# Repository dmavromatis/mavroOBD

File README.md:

# mavroOBD
Arduino (328P) based OBD port module

The goal of this project it to create an Arduino based OBD port module that can be used to enhance a vehicles capabilites.  For example, if you want door locks to close when moving faster than 5mph or to invoke/emulate certain CANbus buttons automatically at start up.

I have uploaded board designs for an OBD module I puchased from China.  It's a two board design.  Lower board solders to the pins of the OBD module and provides a 12V > 5V power supply.  Headers connect to the top board where the Atmel 328P and Microchip MCP2515 CAN Bus controller with SPI interface and MCP2551 CAN transceiver.

This project is based on an Arduino Uno and SeedStudio CAN shield just miniturized to fit in a OBD module.

The module enclousure was purchased from a company in China called AOTAI Industry Co.<br>
Part #: AOT-130N - ODB Connector with housing<br/>
Website: www.aotsisz.com

--------
License
--------

If you are distributing a modified version of the project, please describe the dates and details of your modifications (as described in section 3.3b of the CERN open hardware license).  If you are using a publicly available repository to track changes (which we encourage), you may simply list the URL of the repository here.

https://github.com/dmavromatis/mavroOBD

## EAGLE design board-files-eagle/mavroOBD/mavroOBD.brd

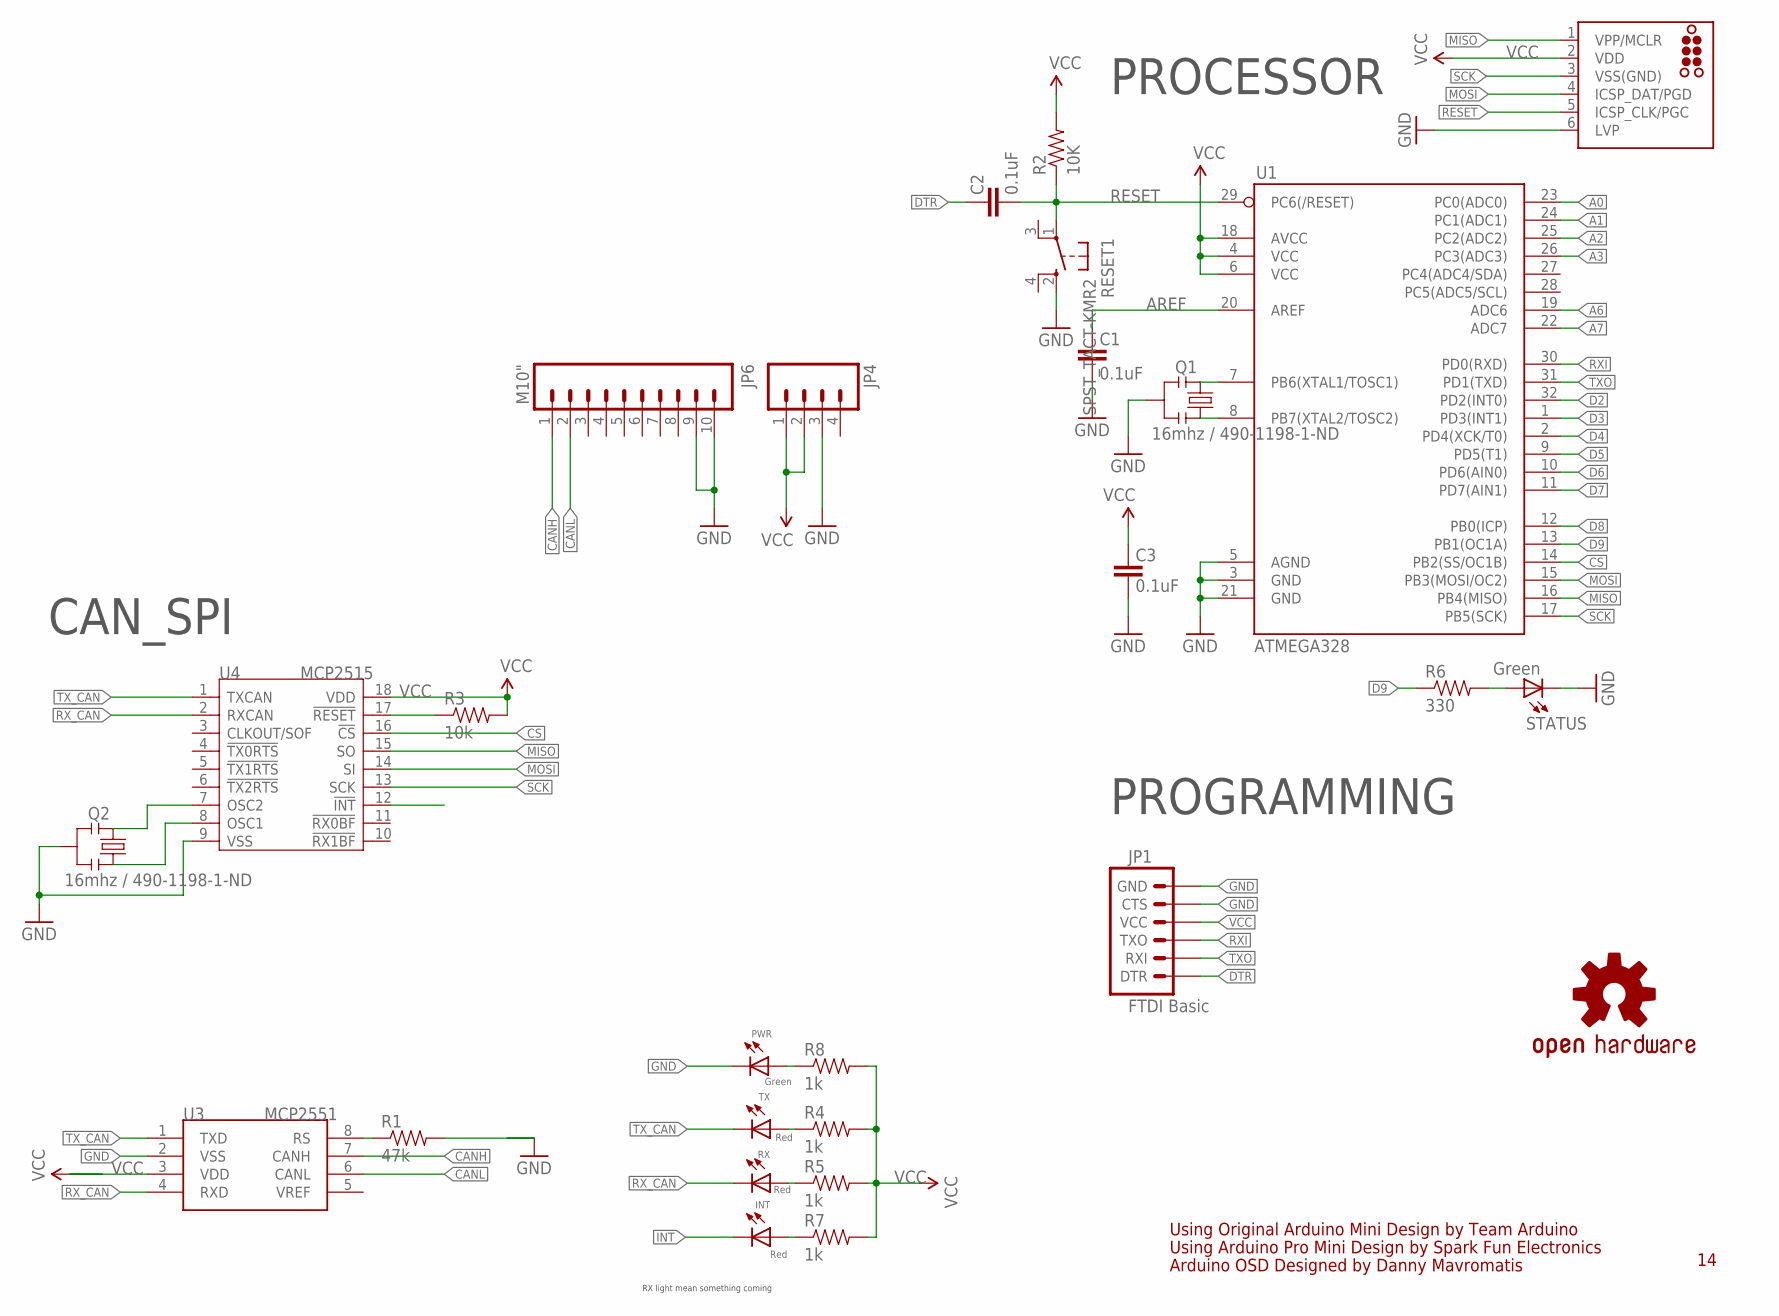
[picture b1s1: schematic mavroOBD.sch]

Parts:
C1, C2, C3: 0.1uF; 0603-CAP
INT: Red; 0603-LED-ALT1
J1: TC2030-MCP-NL
JP1: FTDI Basic; 1X06
JP4: M04PTH; 1X04
JP6: M10"; 1X10
PWR: Green; 0603-LED-ALT1
Q1, Q2: 16mhz / 490-1198-1-ND; RESONATOR-SMD-1:1
R1: 47k; 0603-RES
R2: 10K; 0603-RES
R3: 10k; 0603-RES
R4, R5, R7, R8: 1k; 0603-RES
R6: 330; 0603-RES
RESET1: SPST_TACT-KMR2; KMR2
RX: Red; 0603-LED-ALT1
STATUS: Green; 0603-LED-ALT1
TX: Red; 0603-LED-ALT1
U1: ATMEGA328; TQFP32-08
U3: MCP2551; SOIC8-6.0
U4: MCP2515; SOIC18
U$3: OSHW-LOGOS; OSHW-LOGO-S

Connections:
A0: U1.23 (PC0(ADC0))
A1: U1.24 (PC1(ADC1))
A2: U1.25 (PC2(ADC2))
A3: U1.26 (PC3(ADC3))
A6: U1.19 (ADC6)
A7: U1.22 (ADC7)
AREF: C1.2, U1.20 (AREF)
CANH: JP6.1, U3.7 (CANH)
CANL: JP6.2, U3.6 (CANL)
CS: U1.14 (PB2(SS/OC1B)), U4.16 (!CS)
D2: U1.32 (PD2(INT0))
D3: U1.1 (PD3(INT1))
D4: U1.2 (PD4(XCK/T0))
D5: U1.9 (PD5(T1))
D6: U1.10 (PD6(AIN0))
D7: U1.11 (PD7(AIN1))
D8: U1.12 (PB0(ICP))
D9: R6.1, U1.13 (PB1(OC1A))
DTR: C2.2, JP1.1 (DTR)
GND: C1.1, C3.1, J1.6 (LVP), JP1.5 (CTS), JP1.6 (GND), JP4.3, JP6.9, JP6.10, PWR.C, Q1.2, Q2.2, R1.2, RESET1.2 (S), STATUS.C, U1.3 (GND), U1.5 (AGND), U1.21 (GND), U3.2 (VSS), U4.9 (VSS)
INT: INT.C, U4.12 (!INT)
MISO: J1.1 (VPP/MCLR), U1.16 (PB4(MISO)), U4.15 (SO)
MOSI: J1.4 (ICSP_DAT/PGD), U1.15 (PB3(MOSI/OC2)), U4.14 (SI)
unnamed: Q1.3, U1.8 (PB7(XTAL2/TOSC2))
unnamed: Q1.1, U1.7 (PB6(XTAL1/TOSC1))
unnamed: R4.1, TX.A
unnamed: PWR.A, R8.1
unnamed: R6.2, STATUS.A
unnamed: R5.1, RX.A
unnamed: Q2.1, U4.7 (OSC2)
unnamed: Q2.3, U4.8 (OSC1)
unnamed: INT.A, R7.1
unnamed: R1.1, U3.8 (RS)
RESET: C2.1, J1.5 (ICSP_CLK/PGC), R2.1, RESET1.1, U1.29 (PC6(/RESET))
RST_N: R3.1, U4.17 (!RESET)
RXI: JP1.3 (TXO), U1.30 (PD0(RXD))
RX_CAN: RX.C, U3.4 (RXD), U4.2 (RXCAN)
SCK: J1.3 (VSS(GND)), U1.17 (PB5(SCK)), U4.13 (SCK)
TXO: JP1.2 (RXI), U1.31 (PD1(TXD))
TX_CAN: TX.C, U3.1 (TXD), U4.1 (TXCAN)
VCC: C3.2, J1.2 (VDD), JP1.4 (VCC), JP4.1, JP4.2, R2.2, R3.2, R4.2, R5.2, R7.2, R8.2, U1.4 (VCC), U1.6 (VCC), U1.18 (AVCC), U3.3 (VDD), U4.18 (VDD)

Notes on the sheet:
Using Original Arduino Mini Design by Team Arduino
Using Arduino Pro Mini Design by Spark Fun Electronics
CAN_SPI
RX light mean something coming
PROGRAMMING
PROCESSOR
Arduino OSD Designed by Danny Mavromatis

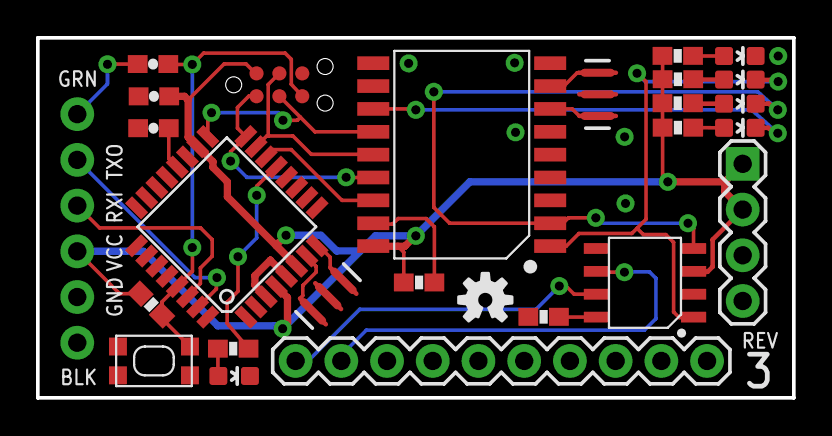
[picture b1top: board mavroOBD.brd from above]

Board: 2 copper layers, 42.0 x 20.0 mm, 27 parts (1 on the bottom side), 28 nets.

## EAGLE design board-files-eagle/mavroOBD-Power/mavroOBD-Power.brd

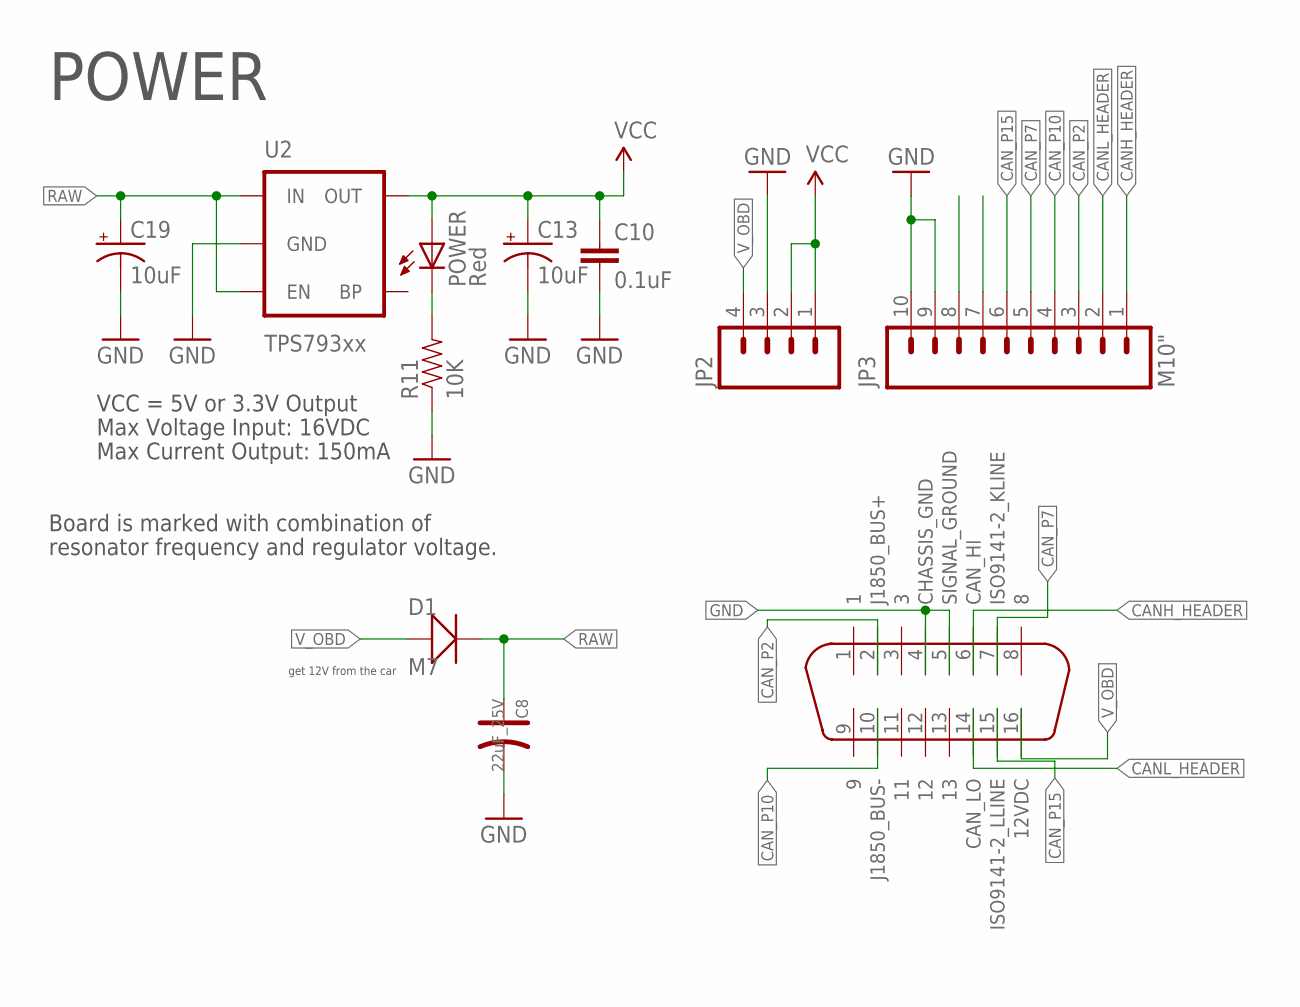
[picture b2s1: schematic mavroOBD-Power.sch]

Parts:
C8: 22uF_25V; ELECTRO-SMD-B-4.8MM
C10: 0.1uF; 0603-CAP
C13, C19: 10uF; EIA3216
D1: M7; D2010
JP2: M04PTH; 1X04
JP3: M10"; 1X10
POWER: Red; 0603-LED-ALT1
R11: 10K; 0603-RES
U2: TPS793xx; SOT23-5
U$1: ODBII-CON; OBDII-CON

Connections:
CANH_HEADER: JP3.1, U$1.6 (CAN_HI)
CANL_HEADER: JP3.2, U$1.14 (CAN_LO)
CAN_P2: JP3.3, U$1.2 (J1850_BUS+)
CAN_P7: JP3.5, U$1.7 (ISO9141-2_KLINE)
CAN_P10: JP3.4, U$1.10 (J1850_BUS-)
CAN_P15: JP3.6, U$1.15 (ISO9141-2_LLINE)
GND: C8.-, C10.2, C13.C (-), C19.C (-), JP2.3, JP3.9, JP3.10, R11.1, U2.2 (GND), U$1.4 (CHASSIS_GND), U$1.5 (SIGNAL_GROUND)
unnamed: POWER.C, R11.2
RAW: C8.+, C19.A (+), D1.-, U2.1 (IN), U2.3 (EN)
VCC_MAIN: C10.1, C13.A (+), JP2.1, JP2.2, POWER.A, U2.5 (OUT)
V_OBD: D1.+, JP2.4, U$1.16 (12VDC)

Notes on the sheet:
Max Voltage Input: 16VDC
Max Current Output: 150mA
Board is marked with combination of
resonator frequency and regulator voltage.
VCC = 5V or 3.3V Output
get 12V from the car
POWER

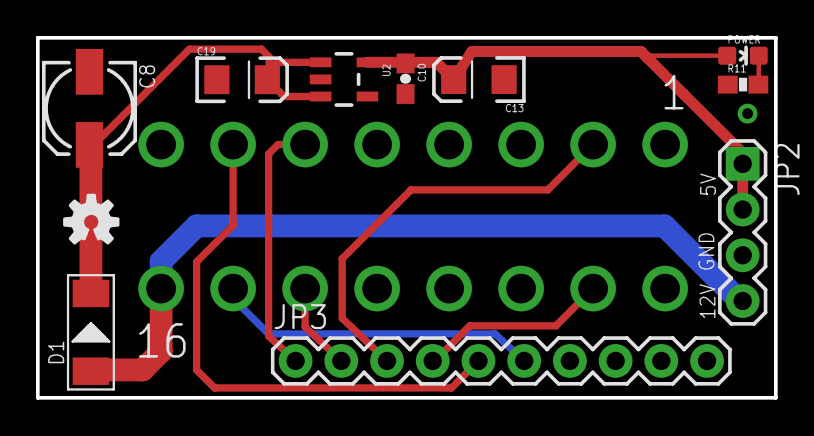
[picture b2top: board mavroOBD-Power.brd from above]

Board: 2 copper layers, 41.0 x 20.0 mm, 12 parts (1 on the bottom side), 11 nets.

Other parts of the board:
U$2: OSHW-LOGOS; OSHW-LOGO-S

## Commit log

2015-12-24 mavroOSD
    Arduino (328P) based OBD port module
2015-12-24 Organizing Files
2015-12-27 Fixed incorrect pin assignment
2015-12-31 Fixed Tag Connect ISP pin assignments
2015-12-31 REV 3 Board - Sent to OSHPark
    Fixed a few via sizes, added VCC to ISP pin and REV 3 to silkscreen.
2016-02-20 Create license.txt
    added license
2016-02-20 Added PDF versions of board schematic

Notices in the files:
parts and their libraries:
SparkFun-Connectors: Licensing: CC v3.0 Share-Alike You are welcome to use this library for commercial purposes.
tag-connect: ©2009 ROFA.cz - modified and updated by Robert Darlington ‹rdarlington@gmail.com›
